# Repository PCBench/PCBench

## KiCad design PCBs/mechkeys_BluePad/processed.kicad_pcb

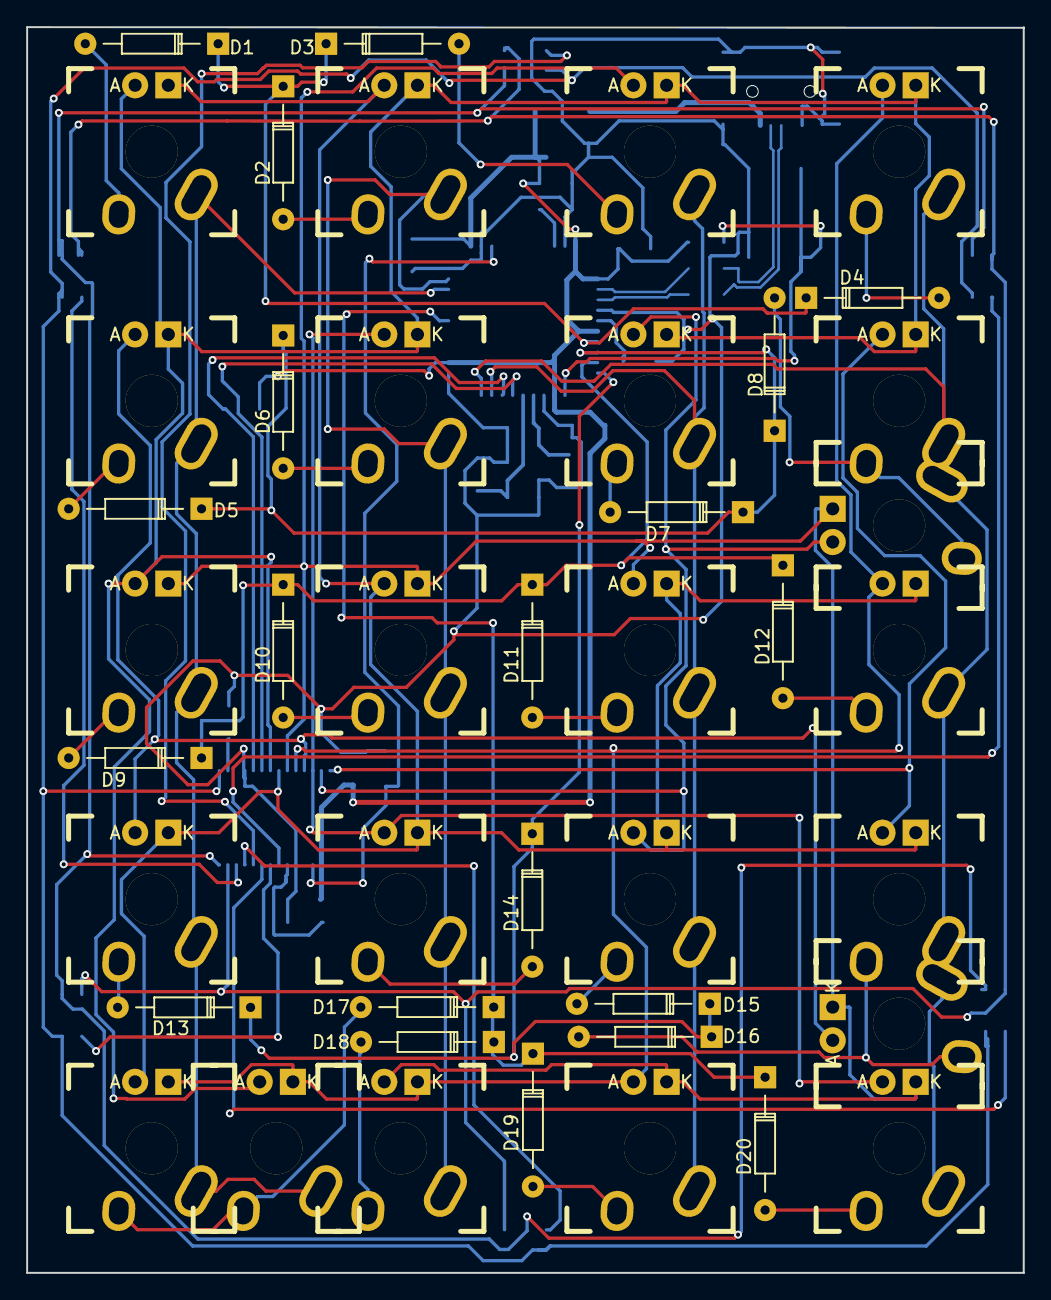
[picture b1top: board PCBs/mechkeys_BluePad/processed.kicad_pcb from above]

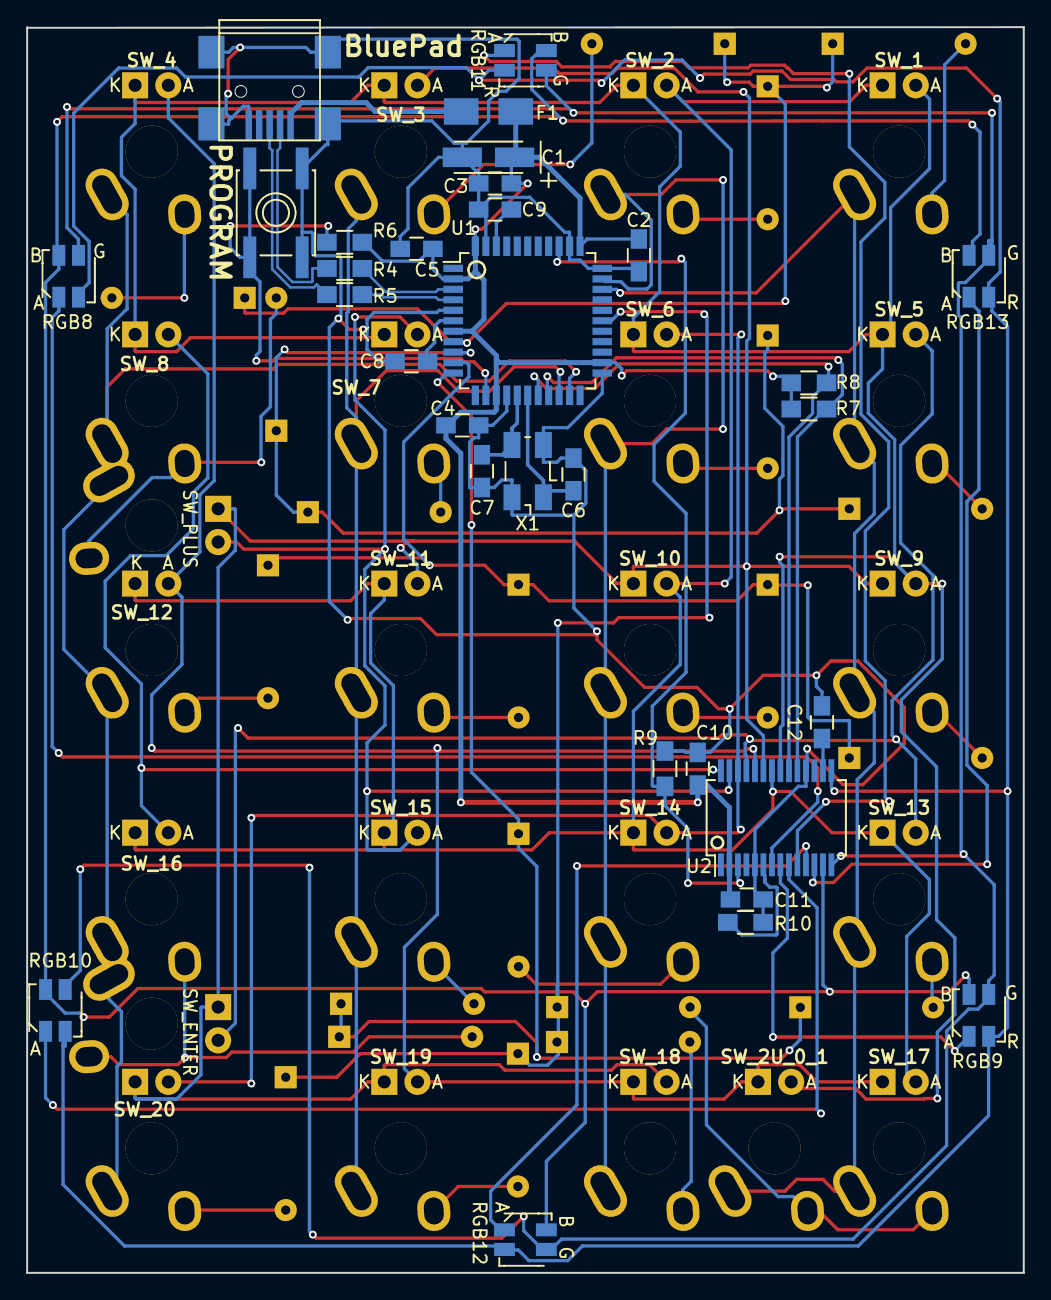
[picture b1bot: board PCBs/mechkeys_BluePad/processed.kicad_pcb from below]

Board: 2 copper layers, 76.2 x 95.2 mm, 74 parts (31 on the bottom side), 63 nets.

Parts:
C1: 10µF; TantalC_SizeA_EIA-3216_HandSoldering
C2, C3, C4, C5, C9, C11, C12: 0.1µF; C_0805_HandSoldering
C6, C7: 18pF; C_0805_HandSoldering
C8, C10: 1µF; C_0805_HandSoldering
D1, D2, D3, D4, D5, D6, D7, D8, D9, D10, D11, D12, D13, D14, D15, D16, D17, D18, D19, D20: D; Diode_DO-35_SOD27_Horizontal_RM10
F1: FP_Small; Fuse_SMD1206_HandSoldering
J1: USB_OTG; USB_Mini-B
R4, R5: 22; R_0805_HandSoldering
R6: 10k; R_0805_HandSoldering
R7, R8: 4.7KΩ; R_0805_HandSoldering
R9: 100KΩ; R_0805_HandSoldering
R10: 20KΩ; R_0805_HandSoldering
RGB8, RGB9, RGB10, RGB11, RGB12, RGB13: Led_RGB_CA; SMP4-RGB
SW1: SW_RST; SW_SPST_EVQP0
SW_1, SW_2, SW_2U_0_1, SW_2U_PLUS_1, SW_3, SW_4, SW_5, SW_6, SW_7, SW_8, SW_9, SW_10, SW_11, SW_12, SW_13, SW_14, SW_15, SW_16, SW_17, SW_18, SW_19, SW_20: MX_LED; MXALPS
SW_2U_ENTER_1: MX_LED; MXALPS_LED_PANEL
U1: ATMEGA32U4RC-A; TQFP-44_10x10mm_Pitch0.8mm
U2: IS31FL3731; SSOP-28_5.3x10.2mm_Pitch0.65mm
X1: 16Mhz; Crystal_SMD_5032_4Pads

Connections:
+5V: C1.1, C2.1, C3.1, C4.1, C5.1, C10.1, C11.1, F1.2, R6.2, R7.1, R8.1, U1.2, U1.7, U1.14, U1.24, U1.34, U1.44, U2.2
C1: SW_1.SW1, SW_2U_0_1.SW1, SW_5.SW1, SW_9.SW1, SW_13.SW1, SW_17.SW1, U1.31
C2: SW_2.SW1, SW_6.SW1, SW_10.SW1, SW_14.SW1, SW_18.SW1, U1.32
C3: SW_3.SW1, SW_7.SW1, SW_11.SW1, SW_15.SW1, SW_19.SW1, U1.20
C4: SW_2U_ENTER_1.SW1, SW_2U_PLUS_1.SW1, SW_4.SW1, SW_8.SW1, SW_12.SW1, SW_16.SW1, SW_20.SW1, U1.21
CA1: SW_1.A, SW_2.K, SW_2U_0_1.A, SW_3.K, SW_4.K, SW_5.K, SW_6.K, SW_7.K, SW_8.K, SW_9.A, U2.21
CA2: SW_1.K, SW_2.A, SW_10.A, SW_11.K, SW_12.K, SW_13.K, SW_14.K, SW_15.K, SW_16.K, SW_17.A, U2.22
CA3: SW_2U_ENTER_1.K, SW_2U_PLUS_1.K, SW_3.A, SW_9.K, SW_10.K, SW_11.A, SW_18.A, SW_19.K, SW_20.K, U2.23
CA4: SW_2U_0_1.K, SW_4.A, SW_12.A, SW_17.K, SW_18.K, SW_19.A, U2.24
CA5: SW_2U_ENTER_1.A, SW_5.A, SW_13.A, U2.25
CA6: SW_6.A, SW_14.A, SW_20.A, U2.26
CA7: SW_2U_PLUS_1.A, SW_7.A, SW_15.A, U2.27
CA8: SW_8.A, SW_16.A, U2.28
CB1: RGB8.1, U2.7
CB2: RGB9.1, U2.8
CB3: RGB10.1, U2.9
CB4: RGB11.1, U2.10
CB5: RGB12.1, U2.11
CB6: RGB13.1, U2.12
CB7: RGB8.4, RGB9.4, RGB10.4, RGB11.4, RGB12.4, RGB13.4, U2.13
CB8: RGB8.3, RGB9.3, RGB10.3, RGB11.3, RGB12.3, RGB13.3, U2.14
CB9: RGB8.2, RGB9.2, RGB10.2, RGB11.2, RGB12.2, RGB13.2, U2.15
D+: R5.1, U1.4
D-: R4.1, U1.3
GND: C1.2, C2.2, C3.2, C4.2, C5.2, C6.2, C7.2, C8.2, C9.2, C10.2, C11.2, C12.2, J1.5, J1.6, R9.2, R10.2, SW1.1, U1.5, U1.15, U1.23, U1.33, U1.35, U1.43, U2.5, U2.18, X1.3
LED_NSRT: R9.1, U1.36, U2.3
LED_SCL: R8.2, U1.18, U2.20
LED_SDA: R7.2, U1.19, U2.19
unnamed: C6.1, U1.17, X1.1
unnamed: C7.1, U1.16, X1.2
unnamed: C8.1, U1.6
unnamed: C9.1, U1.42
unnamed: C12.1, U2.16
unnamed: D1.2, SW_1.SW2
unnamed: D2.2, SW_2.SW2
unnamed: D3.2, SW_3.SW2
unnamed: D4.2, SW_4.SW2
unnamed: D5.2, SW_5.SW2
unnamed: D6.2, SW_6.SW2
unnamed: D7.2, SW_7.SW2
unnamed: D8.2, SW_2U_PLUS_1.SW2, SW_8.SW2
unnamed: D9.2, SW_9.SW2
unnamed: D10.2, SW_10.SW2
unnamed: D11.2, SW_11.SW2
unnamed: D12.2, SW_12.SW2
unnamed: D13.2, SW_13.SW2
unnamed: D14.2, SW_14.SW2
unnamed: D15.2, SW_15.SW2
unnamed: D16.2, SW_2U_ENTER_1.SW2, SW_16.SW2
unnamed: D17.2, SW_2U_0_1.SW2, SW_17.SW2
unnamed: D18.2, SW_18.SW2
unnamed: D19.2, SW_19.SW2
unnamed: D20.2, SW_20.SW2
unnamed: F1.1, J1.1
unnamed: R10.1, U2.6
R1: D1.1, D2.1, D3.1, D4.1, U1.8
R2: D5.1, D6.1, D7.1, D8.1, U1.9
R3: D9.1, D10.1, D11.1, D12.1, U1.10
R4: D13.1, D14.1, D15.1, D16.1, U1.11
R5: D17.1, D18.1, D19.1, D20.1, U1.28
RST: R6.1, SW1.2, U1.13
USB+: J1.3, R5.2
USB-: J1.2, R4.2

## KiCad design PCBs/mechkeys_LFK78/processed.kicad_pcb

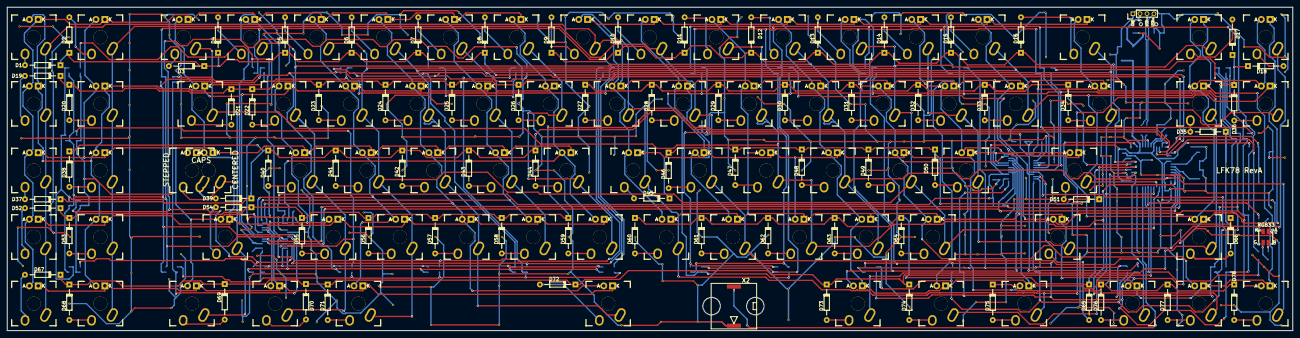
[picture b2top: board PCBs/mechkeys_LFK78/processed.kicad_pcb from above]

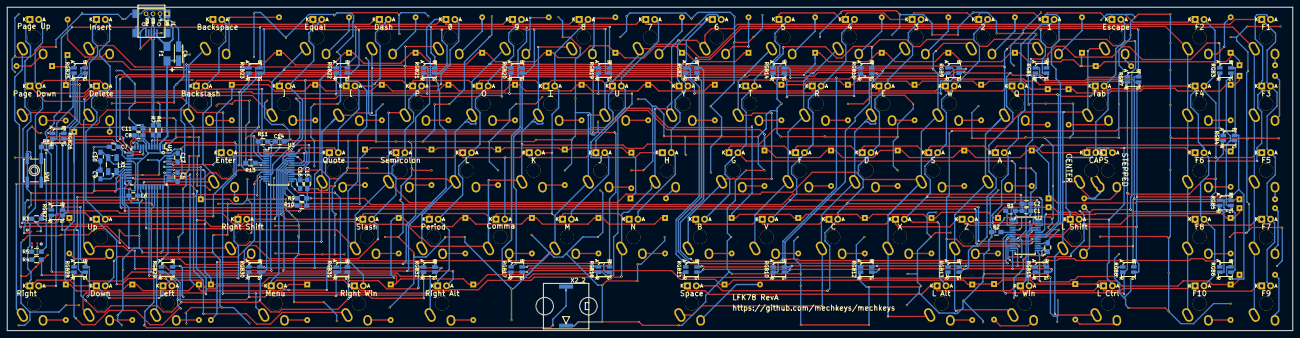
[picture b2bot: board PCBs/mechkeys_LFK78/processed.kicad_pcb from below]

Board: 2 copper layers, 367.8 x 92.5 mm, 226 parts (66 on the bottom side), 159 nets.

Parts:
C1, C11, C14: 1µF; C_0805_HandSoldering
C2, C3, C5, C6, C7, C8, C12, C15, C16: 0.1µF; C_0805_HandSoldering
C4: 10µF; TantalC_SizeA_EIA-3216_HandSoldering
C9, C10: 18pF; C_0805_HandSoldering
CHERRY: MX; CHERRY_PCB_625H_STABILIZER
D1, D2, D3, D4, D5, D6, D7, D8, D9, D10, D11, D12, D13, D14, D15, D16, D17, D18, D19, D20, D21, D22, D23, D24, D25, D26, D27, D28, D29, D30, D31, D32, D33, D34, D35, D36, D37, D38, D39, D40, D41, D42, D43, D44, D45, D46, D47, D48, D49, D50, D51, D52, D53, D54, D55, D56, D57, D58, D59, D60, D61, D62, D63, D64, D65, D66, D67, D68, D69, D70, D71, D72, D73, D74, D75, D76, D77, D78: D; Diode_DO-35_SOD27_Horizontal_RM10
F1: FP_Small; Fuse_SMD1206_HandSoldering
J1: USB_OTG; USB_Mini-B
R1, R11: 10KΩ; R_0805_HandSoldering
R2, R13: 20KΩ; R_0805_HandSoldering
R3: 150Ω; R_0805_HandSoldering
R4, R5: 120Ω; R_0805_HandSoldering
R6, R7: 22; R_0805_HandSoldering
R8: 10k; R_0805_HandSoldering
R9, R10: 4.7KΩ; R_0805_HandSoldering
RGB1, RGB2, RGB3, RGB4, RGB5, RGB6, RGB7, RGB8, RGB9, RGB10, RGB11, RGB12, RGB13, RGB14, RGB15, RGB16, RGB17, RGB18, RGB19, RGB20, RGB21, RGB22, RGB23, RGB25, RGB26, RGB27, RGB28, RGB29, RGB30, RGB31, RGB32: Led_RGB_CA; SMP4-RGB
RGB33: Led_RGB_CA; SMP4-RGB-PIPE
SW1: SW_RST; SW_SPST_EVQP0
SW_A_40: MX_LED; MXALPS_LED_PANEL
SW_Alt_71, SW_Alt_73: MX_LED; MXALPS_LED_PANEL
SW_B_59: MX_LED; MXALPS_LED_PANEL
SW_Backspace_16: MX_LED; MXALPS_LED_PANEL
SW_C_57: MX_LED; MXALPS_LED_PANEL
SW_CapStep_39: MX_LED; MXALPS_LED_PANEL
SW_Caps_39: MX_LED; MXALPS_LED_PANEL
SW_Ctrl_69: MX_LED; MXALPS_LED_PANEL
SW_D_42: MX_LED; MXALPS_LED_PANEL
SW_Del_35: MX_LED; MXALPS_LED_PANEL
SW_E_24: MX_LED; MXALPS_LED_PANEL
SW_Enter_51: MX_LED; MXALPS_LED_PANEL
SW_F1_1, SW_F2_2, SW_F3_19, SW_F4_20, SW_F5_37, SW_F6_38, SW_F7_52, SW_F8_53, SW_F9_67, SW_F10_68: MX_LED; MXALPS_LED_PANEL
SW_F_43: MX_LED; MXALPS_LED_PANEL
SW_G_44: MX_LED; MXALPS_LED_PANEL
SW_H_45: MX_LED; MXALPS_LED_PANEL
SW_I_29: MX_LED; MXALPS_LED_PANEL
SW_Ins_17: MX_LED; MXALPS_LED_PANEL
SW_J_46: MX_LED; MXALPS_LED_PANEL
SW_K_47: MX_LED; MXALPS_LED_PANEL
SW_L_48: MX_LED; MXALPS_LED_PANEL
SW_M_61: MX_LED; MXALPS_LED_PANEL
SW_Menu_75: MX_LED; MXALPS_LED_PANEL
SW_N_60: MX_LED; MXALPS_LED_PANEL
SW_O_30: MX_LED; MXALPS_LED_PANEL
SW_P_31: MX_LED; MXALPS_LED_PANEL
SW_PgDn_36: MX_LED; MXALPS_LED_PANEL
SW_PgUp_18: MX_LED; MXALPS_LED_PANEL
SW_Q_22: MX_LED; MXALPS_LED_PANEL
SW_R_25: MX_LED; MXALPS_LED_PANEL
SW_S_41: MX_LED; MXALPS_LED_PANEL
SW_Shift_54, SW_Shift_65: MX_LED; MXALPS_LED_PANEL
SW_T_26: MX_LED; MXALPS_LED_PANEL
SW_Tab_21: MX_LED; MXALPS_LED_PANEL
SW_U_28: MX_LED; MXALPS_LED_PANEL
SW_V_58: MX_LED; MXALPS_LED_PANEL
SW_W_23: MX_LED; MXALPS_LED_PANEL
SW_Win_70, SW_Win_74: MX_LED; MXALPS_LED_PANEL
SW_X4Y1_3, SW_X5Y1_4, SW_X6Y1_5, SW_X7Y1_6, SW_X8Y1_7, SW_X8Y5_72, SW_X9Y1_8, SW_X10Y1_9, SW_X11Y1_10, SW_X12Y1_11, SW_X13Y1_12, SW_X13Y4_62, SW_X14Y1_13, SW_X14Y4_63, SW_X15Y1_14, SW_X15Y2_32, SW_X15Y3_49, SW_X15Y4_64, SW_X16Y1_15, SW_X16Y2_33, SW_X16Y3_50, SW_X17Y2_34, SW_X18Y5_76, SW_X19Y4_66, SW_X19Y5_77, SW_X20Y5_78: MX_LED; MXALPS_LED_PANEL
SW_X_56: MX_LED; MXALPS_LED_PANEL
SW_Y_27: MX_LED; MXALPS_LED_PANEL
SW_Z_55: MX_LED; MXALPS_LED_PANEL
U1: ATMEGA32U4RC-A; TQFP-44_10x10mm_Pitch0.8mm
U2, U3: IS31FL3731; SSOP-28_5.3x10.2mm_Pitch0.65mm
X1: 16Mhz; Crystal_SMD_5032_4Pads
X2, X2_2: PiezoelectricCrystal-TwoElectrodes_EN60617_04-07-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; piezo-12x12

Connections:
+5V: C1.1, C2.1, C4.1, C5.1, C6.1, C7.1, C8.1, C14.1, C15.1, F1.2, R1.2, R8.2, R9.1, R10.1, R11.2, RGB33.1, U1.2, U1.7, U1.14, U1.24, U1.34, U1.44, U2.2, U3.2, U3.18
AUDIO: U1.31, X2.2, X2_2.2
C1: SW_F1_1.SW1, SW_F3_19.SW1, SW_F5_37.SW1, SW_F7_52.SW1, SW_F9_67.SW1, SW_H_45.SW1, SW_Menu_75.SW1, SW_N_60.SW1, SW_X10Y1_9.SW1, SW_Y_27.SW1, U1.1
C2: SW_F2_2.SW1, SW_F4_20.SW1, SW_F6_38.SW1, SW_F8_53.SW1, SW_F10_68.SW1, SW_J_46.SW1, SW_M_61.SW1, SW_U_28.SW1, SW_X11Y1_10.SW1, SW_X18Y5_76.SW1, U1.36
C3: SW_CapStep_39.SW2, SW_Caps_39.SW1, SW_Ctrl_69.SW1, SW_I_29.SW1, SW_K_47.SW1, SW_Shift_54.SW1, SW_Tab_21.SW1, SW_X4Y1_3.SW1, SW_X12Y1_11.SW1, SW_X13Y4_62.SW1, SW_X19Y5_77.SW1, U1.20
C4: SW_A_40.SW1, SW_L_48.SW1, SW_O_30.SW1, SW_Q_22.SW1, SW_Win_70.SW1, SW_X5Y1_4.SW1, SW_X13Y1_12.SW1, SW_X14Y4_63.SW1, SW_X20Y5_78.SW1, SW_Z_55.SW1, U1.21
C5: SW_Alt_71.SW1, SW_Ins_17.SW1, SW_P_31.SW1, SW_S_41.SW1, SW_W_23.SW1, SW_X6Y1_5.SW1, SW_X14Y1_13.SW1, SW_X15Y3_49.SW1, SW_X15Y4_64.SW1, SW_X_56.SW1, U1.25
C6: SW_C_57.SW1, SW_D_42.SW1, SW_E_24.SW1, SW_PgUp_18.SW1, SW_Shift_65.SW1, SW_X7Y1_6.SW1, SW_X8Y5_72.SW1, SW_X15Y1_14.SW1, SW_X15Y2_32.SW1, SW_X16Y3_50.SW1, U1.22
C7: SW_Alt_73.SW1, SW_Del_35.SW1, SW_Enter_51.SW1, SW_F_43.SW1, SW_R_25.SW1, SW_V_58.SW1, SW_X8Y1_7.SW1, SW_X16Y1_15.SW1, SW_X16Y2_33.SW1, SW_X19Y4_66.SW1, U1.26
C8: SW_B_59.SW1, SW_Backspace_16.SW1, SW_G_44.SW1, SW_PgDn_36.SW1, SW_T_26.SW1, SW_Win_74.SW1, SW_X9Y1_8.SW1, SW_X17Y2_34.SW1, U1.27
D+: R7.1, U1.4
D-: R6.1, U1.3
GND: C1.2, C2.2, C3.2, C4.2, C5.2, C6.2, C7.2, C8.2, C9.2, C10.2, C11.2, C12.2, C14.2, C15.2, C16.2, J1.5, J1.6, R2.2, R13.2, SW1.1, U1.5, U1.15, U1.23, U1.33, U1.35, U1.43, U2.5, U2.18, U3.5, X2.1, X2_2.1
LED_SCL: R10.2, U1.18, U2.20, U3.20
LED_SDA: R9.2, U1.19, U2.19, U3.19
L_CA1: SW_F1_1.K, SW_F2_2.K, SW_F3_19.A, SW_F5_37.A, SW_F7_52.A, SW_F9_67.A, SW_X4Y1_3.K, SW_X5Y1_4.K, SW_X6Y1_5.K, SW_X7Y1_6.K, SW_X8Y1_7.K, SW_X9Y1_8.K, U2.21
L_CA2: SW_E_24.K, SW_F1_1.A, SW_F3_19.K, SW_F4_20.K, SW_F6_38.A, SW_F8_53.A, SW_F10_68.A, SW_Q_22.K, SW_R_25.K, SW_T_26.K, SW_Tab_21.K, SW_W_23.K, U2.22
L_CA3: SW_A_40.K, SW_CapStep_39.K, SW_Caps_39.K, SW_Ctrl_69.A, SW_D_42.K, SW_F2_2.A, SW_F4_20.A, SW_F5_37.K, SW_F6_38.K, SW_F_43.K, SW_G_44.K, SW_S_41.K, SW_Shift_54.A, U2.23
L_CA4: SW_B_59.K, SW_C_57.K, SW_CapStep_39.A, SW_Caps_39.A, SW_F7_52.K, SW_F8_53.K, SW_Shift_54.K, SW_Tab_21.A, SW_V_58.K, SW_Win_70.A, SW_X4Y1_3.A, SW_X_56.K, SW_Z_55.K, U2.24
L_CA5: SW_A_40.A, SW_Alt_71.K, SW_Ctrl_69.K, SW_F9_67.K, SW_F10_68.K, SW_Q_22.A, SW_Win_70.K, SW_X5Y1_4.A, SW_X8Y5_72.K, SW_Z_55.A, U2.25
L_CA6: SW_Alt_71.A, SW_S_41.A, SW_W_23.A, SW_X6Y1_5.A, SW_X_56.A, U2.26
L_CA7: SW_C_57.A, SW_D_42.A, SW_E_24.A, SW_X7Y1_6.A, SW_X8Y5_72.A, U2.27
L_CA8: SW_F_43.A, SW_R_25.A, SW_V_58.A, SW_X8Y1_7.A, U2.28
L_CA9: SW_B_59.A, SW_G_44.A, SW_T_26.A, SW_X9Y1_8.A, U2.1
L_CB1: RGB1.2, RGB2.2, RGB3.2, RGB4.2, RGB5.2, RGB6.2, RGB7.2, RGB8.2, RGB9.1, U2.7
L_CB2: RGB1.1, RGB2.3, RGB3.3, RGB4.3, RGB5.3, RGB6.3, RGB7.3, RGB8.3, RGB10.1, U2.8
L_CB3: RGB1.3, RGB2.1, RGB3.4, RGB4.4, RGB5.4, RGB6.4, RGB7.4, RGB8.4, RGB11.1, U2.9
L_CB4: RGB1.4, RGB2.4, RGB3.1, RGB12.1, U2.10
L_CB5: RGB4.1, RGB13.1, U2.11
L_CB6: RGB5.1, RGB14.1, RGB15.4, RGB16.4, U2.12
L_CB7: RGB6.1, RGB9.4, RGB10.4, RGB11.4, RGB12.4, RGB13.4, RGB14.4, RGB15.1, RGB16.3, U2.13
L_CB8: RGB7.1, RGB9.3, RGB10.3, RGB11.3, RGB12.3, RGB13.3, RGB14.3, RGB15.3, RGB16.1, U2.14
L_CB9: RGB8.1, RGB9.2, RGB10.2, RGB11.2, RGB12.2, RGB13.2, RGB14.2, RGB15.2, RGB16.2, U2.15
unnamed: C3.1, U2.16
unnamed: C9.1, U1.17, X1.1
unnamed: C10.1, U1.16, X1.2
unnamed: C11.1, U1.6
unnamed: C12.1, U1.42
unnamed: C16.1, U3.16
unnamed: D1.2, SW_F1_1.SW2
unnamed: D2.2, SW_F2_2.SW2
unnamed: D3.2, SW_X4Y1_3.SW2
unnamed: D4.2, SW_X5Y1_4.SW2
unnamed: D5.2, SW_X6Y1_5.SW2
unnamed: D6.2, SW_X7Y1_6.SW2
unnamed: D7.2, SW_X8Y1_7.SW2
unnamed: D8.2, SW_X9Y1_8.SW2
unnamed: D9.2, SW_X10Y1_9.SW2
unnamed: D10.2, SW_X11Y1_10.SW2
unnamed: D11.2, SW_X12Y1_11.SW2
unnamed: D12.2, SW_X13Y1_12.SW2
unnamed: D13.2, SW_X14Y1_13.SW2
unnamed: D14.2, SW_X15Y1_14.SW2
unnamed: D15.2, SW_X16Y1_15.SW2
unnamed: D16.2, SW_Backspace_16.SW2
unnamed: D17.2, SW_Ins_17.SW2
unnamed: D18.2, SW_PgUp_18.SW2
unnamed: D19.2, SW_F3_19.SW2
unnamed: D20.2, SW_F4_20.SW2
unnamed: D21.2, SW_Tab_21.SW2
unnamed: D22.2, SW_Q_22.SW2
unnamed: D23.2, SW_W_23.SW2
unnamed: D24.2, SW_E_24.SW2
unnamed: D25.2, SW_R_25.SW2
unnamed: D26.2, SW_T_26.SW2
unnamed: D27.2, SW_Y_27.SW2
unnamed: D28.2, SW_U_28.SW2
unnamed: D29.2, SW_I_29.SW2
unnamed: D30.2, SW_O_30.SW2
unnamed: D31.2, SW_P_31.SW2
unnamed: D32.2, SW_X15Y2_32.SW2
unnamed: D33.2, SW_X16Y2_33.SW2
unnamed: D34.2, SW_X17Y2_34.SW2
unnamed: D35.2, SW_Del_35.SW2
unnamed: D36.2, SW_PgDn_36.SW2
unnamed: D37.2, SW_F5_37.SW2
unnamed: D38.2, SW_F6_38.SW2
unnamed: D39.2, SW_CapStep_39.SW1, SW_Caps_39.SW2
unnamed: D40.2, SW_A_40.SW2
unnamed: D41.2, SW_S_41.SW2
unnamed: D42.2, SW_D_42.SW2
unnamed: D43.2, SW_F_43.SW2
unnamed: D44.2, SW_G_44.SW2
unnamed: D45.2, SW_H_45.SW2
unnamed: D46.2, SW_J_46.SW2
unnamed: D47.2, SW_K_47.SW2
unnamed: D48.2, SW_L_48.SW2
unnamed: D49.2, SW_X15Y3_49.SW2
unnamed: D50.2, SW_X16Y3_50.SW2
unnamed: D51.2, SW_Enter_51.SW2
unnamed: D52.2, SW_F7_52.SW2
unnamed: D53.2, SW_F8_53.SW2
unnamed: D54.2, SW_Shift_54.SW2
unnamed: D55.2, SW_Z_55.SW2
unnamed: D56.2, SW_X_56.SW2
unnamed: D57.2, SW_C_57.SW2
unnamed: D58.2, SW_V_58.SW2
unnamed: D59.2, SW_B_59.SW2
unnamed: D60.2, SW_N_60.SW2
unnamed: D61.2, SW_M_61.SW2
unnamed: D62.2, SW_X13Y4_62.SW2
unnamed: D63.2, SW_X14Y4_63.SW2
unnamed: D64.2, SW_X15Y4_64.SW2
unnamed: D65.2, SW_Shift_65.SW2
unnamed: D66.2, SW_X19Y4_66.SW2
unnamed: D67.2, SW_F9_67.SW2
unnamed: D68.2, SW_F10_68.SW2
unnamed: D69.2, SW_Ctrl_69.SW2
unnamed: D70.2, SW_Win_70.SW2
unnamed: D71.2, SW_Alt_71.SW2
unnamed: D72.2, SW_X8Y5_72.SW2
unnamed: D73.2, SW_Alt_73.SW2
unnamed: D74.2, SW_Win_74.SW2
unnamed: D75.2, SW_Menu_75.SW2
unnamed: D76.2, SW_X18Y5_76.SW2
unnamed: D77.2, SW_X19Y5_77.SW2
unnamed: D78.2, SW_X20Y5_78.SW2
unnamed: F1.1, J1.1
unnamed: R1.1, U2.3
unnamed: R2.1, U2.6
unnamed: R3.1, RGB33.2
unnamed: R4.1, RGB33.3
unnamed: R5.1, RGB33.4
unnamed: R11.1, U3.3
unnamed: R13.1, U3.6
PWM_BLUE: R5.2, U1.12
PWM_GREEN: R4.2, U1.30
PWM_RED: R3.2, U1.29
R1: D1.1, D2.1, D3.1, D4.1, D5.1, D6.1, D7.1, D8.1, U1.8
R2/SCK: D19.1, D20.1, D21.1, D22.1, D23.1, D24.1, D25.1, D26.1, U1.9
R3/MOSI: D37.1, D38.1, D39.1, D40.1, D41.1, D42.1, D43.1, D44.1, U1.10
R4/MISO: D52.1, D53.1, D54.1, D55.1, D56.1, D57.1, D58.1, D59.1, U1.11
R5: D67.1, D68.1, D69.1, D70.1, D71.1, D72.1, D73.1, D74.1, U1.28
R6: D9.1, D10.1, D11.1, D12.1, D13.1, D14.1, D15.1, D16.1, U1.41
R7: D27.1, D28.1, D29.1, D30.1, D31.1, D32.1, D33.1, D34.1, U1.40
R8: D45.1, D46.1, D47.1, D48.1, D49.1, D50.1, D51.1, U1.39
R9: D60.1, D61.1, D62.1, D63.1, D64.1, D65.1, D66.1, U1.38
R10: D17.1, D18.1, D35.1, D36.1, D75.1, D76.1, D77.1, D78.1, U1.37
RST: R8.1, SW1.2, U1.13
R_CA1: SW_Alt_73.A, SW_Backspace_16.K, SW_H_45.A, SW_N_60.A, SW_X10Y1_9.K, SW_X11Y1_10.K, SW_X12Y1_11.K, SW_X13Y1_12.K, SW_X14Y1_13.K, SW_X15Y1_14.K, SW_X16Y1_15.K, SW_Y_27.A, U3.21
R_CA2: SW_I_29.K, SW_J_46.A, SW_M_61.A, SW_O_30.K, SW_P_31.K, SW_U_28.K, SW_Win_74.A, SW_X10Y1_9.A, SW_X15Y2_32.K, SW_X16Y2_33.K, SW_X17Y2_34.K, SW_Y_27.K, U3.22
R_CA3: SW_Enter_51.K, SW_H_45.K, SW_J_46.K, SW_K_47.K, SW_L_48.K, SW_Menu_75.A, SW_PgDn_36.K, SW_U_28.A, SW_X11Y1_10.A, SW_X13Y4_62.A, SW_X15Y3_49.K, SW_X16Y3_50.K, U3.23
R_CA4: SW_I_29.A, SW_K_47.A, SW_M_61.K, SW_N_60.K, SW_PgUp_18.K, SW_Shift_65.K, SW_X12Y1_11.A, SW_X13Y4_62.K, SW_X14Y4_63.K, SW_X15Y4_64.K, SW_X18Y5_76.A, SW_X19Y4_66.K, U3.24
R_CA5: SW_Alt_73.K, SW_Del_35.K, SW_Ins_17.K, SW_L_48.A, SW_Menu_75.K, SW_O_30.A, SW_Win_74.K, SW_X13Y1_12.A, SW_X14Y4_63.A, SW_X18Y5_76.K, SW_X19Y5_77.K, SW_X20Y5_78.K, U3.25
R_CA6: SW_P_31.A, SW_X14Y1_13.A, SW_X15Y3_49.A, SW_X15Y4_64.A, SW_X19Y5_77.A, U3.26
R_CA7: SW_Shift_65.A, SW_X15Y1_14.A, SW_X15Y2_32.A, SW_X16Y3_50.A, SW_X20Y5_78.A, U3.27
R_CA8: SW_Enter_51.A, SW_Ins_17.A, SW_X16Y1_15.A, SW_X16Y2_33.A, SW_X19Y4_66.A, U3.28
R_CA9: SW_Backspace_16.A, SW_Del_35.A, SW_PgDn_36.A, SW_PgUp_18.A, SW_X17Y2_34.A, U3.1
R_CB1: RGB17.2, RGB18.2, RGB19.2, RGB20.2, RGB21.2, RGB22.2, RGB23.2, RGB25.1, U3.7
R_CB2: RGB17.1, RGB18.3, RGB19.3, RGB20.3, RGB21.3, RGB22.3, RGB23.3, RGB26.1, U3.8
R_CB3: RGB17.3, RGB18.1, RGB19.4, RGB20.4, RGB21.4, RGB22.4, RGB23.4, RGB27.1, U3.9
R_CB4: RGB17.4, RGB18.4, RGB19.1, RGB28.1, U3.10
R_CB5: RGB20.1, RGB29.1, U3.11
R_CB6: RGB21.1, RGB30.1, RGB31.4, RGB32.4, U3.12
R_CB7: RGB22.1, RGB25.4, RGB26.4, RGB27.4, RGB28.4, RGB29.4, RGB30.4, RGB31.1, RGB32.3, U3.13
R_CB8: RGB23.1, RGB25.3, RGB26.3, RGB27.3, RGB28.3, RGB29.3, RGB30.3, RGB31.3, RGB32.1, U3.14
R_CB9: RGB25.2, RGB26.2, RGB27.2, RGB28.2, RGB29.2, RGB30.2, RGB31.2, RGB32.2, U3.15
USB+: J1.3, R7.2
USB-: J1.2, R6.2

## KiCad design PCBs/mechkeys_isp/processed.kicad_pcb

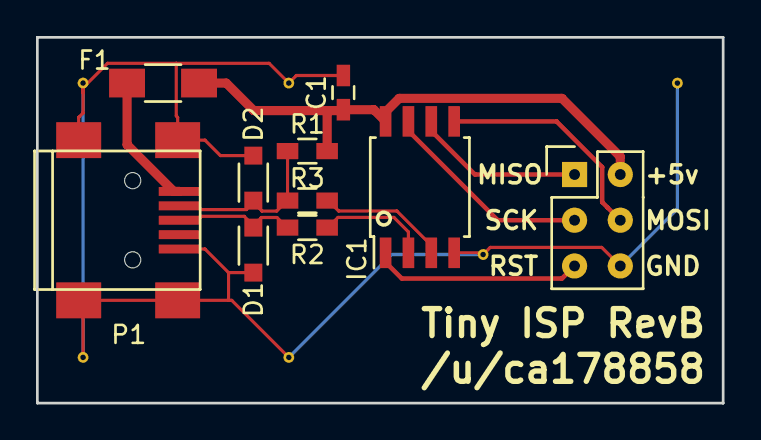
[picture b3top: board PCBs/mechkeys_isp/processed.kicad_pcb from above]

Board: 2 copper layers, 38.1 x 20.3 mm, 10 parts (0 on the bottom side), 11 nets.

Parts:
C1: 0.1µF; C_0603_HandSoldering
D1, D2: 3.6v; SOD-323_HandSoldering
F1: F_Small; C_1206_HandSoldering
IC1: ATTINY45-S; SOIJ-8_5.3x5.3mm_Pitch1.27mm
P1: USB_OTG; USB_Mini-B
P2: CONN_02X03; Pin_Header_Straight_2x03
R1: 1.7kΩ; R_0603_HandSoldering
R2, R3: 68Ω; R_0603_HandSoldering

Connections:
+5V: C1.1, F1.1, IC1.8, P2.2, R1.1
D+: D1.1, P1.3, R2.2
D-: D2.1, P1.2, R1.2, R3.2
GND: C1.2, D1.2, D2.2, IC1.4, P1.5, P1.6, P2.6
MISO: IC1.6, P2.1
MOSI: IC1.5, P2.4
unnamed: F1.2, P1.1
unnamed: IC1.2, R2.1
unnamed: IC1.3, R3.1
RST: IC1.1, P2.5
SCK: IC1.7, P2.3

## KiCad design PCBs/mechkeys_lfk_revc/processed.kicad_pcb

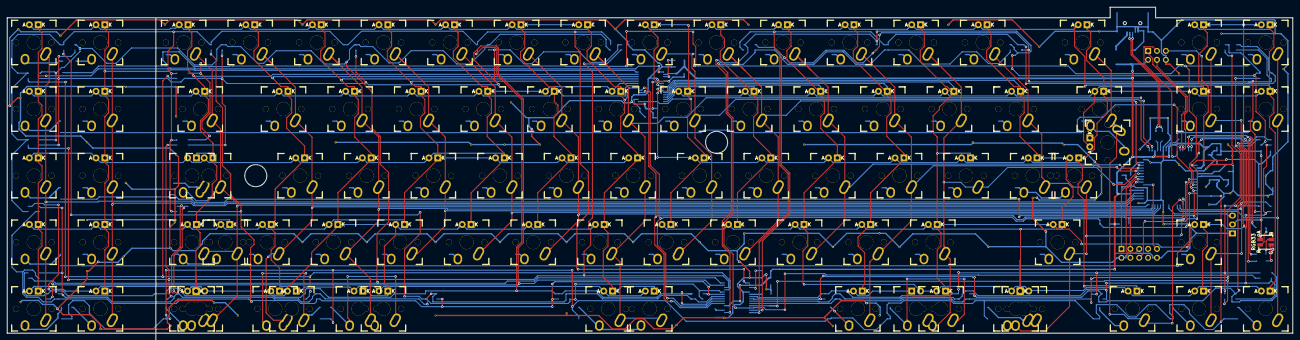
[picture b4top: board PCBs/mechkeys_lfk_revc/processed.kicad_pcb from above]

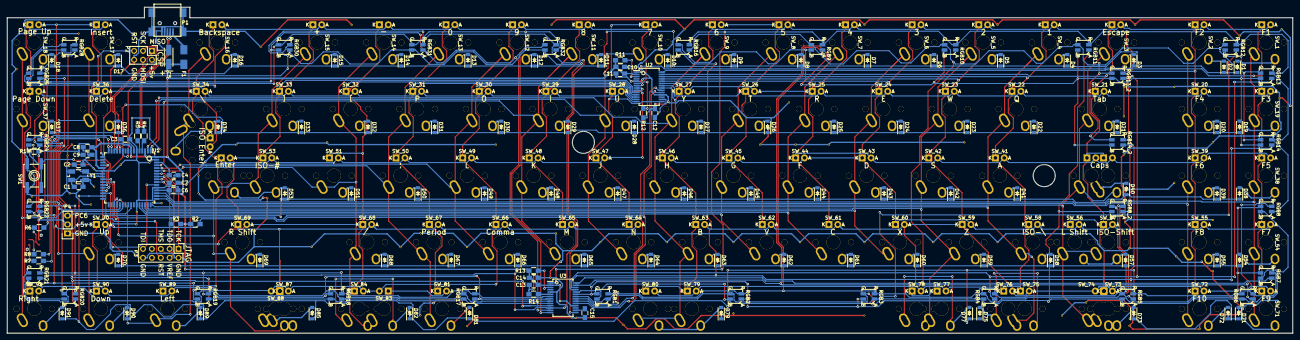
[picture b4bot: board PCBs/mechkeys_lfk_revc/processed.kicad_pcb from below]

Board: 2 copper layers, 367.8 x 93.2 mm, 238 parts (146 on the bottom side), 172 nets.

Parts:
C1, C2: 18pF; C_0805_HandSoldering
C3, C6, C7, C8, C9, C11, C12, C14, C15: 0.1µF; C_0805_HandSoldering
C4, C10, C13: 1µF; C_0805_HandSoldering
C5: 4.7µF; TantalC_SizeA_EIA-3216_HandSoldering
D1, D2, D3, D4, D5, D6, D7, D8, D9, D10, D11, D12, D13, D14, D15, D16, D17, D18, D19, D20, D21, D22, D23, D24, D25, D26, D27, D28, D29, D30, D31, D32, D33, D34, D36, D37, D38, D39, D40, D41, D42, D43, D44, D45, D46, D47, D48, D49, D50, D51, D53, D54, D55, D57, D58, D59, D60, D61, D62, D63, D64, D65, D66, D67, D68, D69, D70, D71, D72, D73, D75, D77, D79, D81, D82, D85, D89, D90, D91: D; SOD-123
F1: FP_Small; Fuse_SMD1206_HandSoldering
P1: USB_B; USB_Mini-B
P2: CONN_02X03; Pin_Header_Straight_2x03
P3: CONN_02X05; Pin_Header_Straight_2x05
P4: CONN_01X03; Pin_Header_Straight_1x03
R1: 10kΩ; R_0805_HandSoldering
R2, R3: 4.7kΩ; R_0805_HandSoldering
R4, R5: 22Ω; R_0805_HandSoldering
R6: 150; R_0805_HandSoldering
R7, R8: 120; R_0805_HandSoldering
R11, R13: 10KΩ; R_0805_HandSoldering
R12, R14: 20KΩ; R_0805_HandSoldering
RGB1, RGB2, RGB3, RGB4, RGB5, RGB6, RGB7, RGB8, RGB8_2, RGB9, RGB10, RGB11, RGB12, RGB13, RGB13_2, RGB14, RGB14_2, RGB16, RGB17, RGB18, RGB19, RGB20, RGB21, RGB22, RGB24, RGB25, RGB28, RGB30, RGB31, RGB32: Led_RGB_CA; SMP4-RGB
RGB33: Led_RGB_CA; SMP4-RGB-PIPE
STA: Stabilizer; CHERRY_PCB_200_STABILIZER_OUTLINE
STA_2: Stabilizer; CHERRY_PCB_200_STABILIZER_OUTLINE
SW1: SW_PUSH; SW_SPST_EVQP0
SW_1, SW_2, SW_3, SW_4, SW_5, SW_6, SW_7, SW_8, SW_9, SW_10, SW_11, SW_12, SW_13, SW_14, SW_15, SW_16, SW_17, SW_18, SW_19, SW_20, SW_21, SW_22, SW_23, SW_24, SW_25, SW_26, SW_27, SW_28, SW_29, SW_30, SW_31, SW_32, SW_33, SW_34, SW_35, SW_36, SW_37, SW_38, SW_39, SW_40, SW_40_2, SW_41, SW_42, SW_43, SW_44, SW_45, SW_46, SW_47, SW_48, SW_49, SW_50, SW_51, SW_52, SW_53, SW_54, SW_55, SW_56, SW_57, SW_58, SW_59, SW_60, SW_61, SW_62, SW_63, SW_64, SW_65, SW_66, SW_67, SW_68, SW_69, SW_70, SW_71, SW_72, SW_73, SW_75, SW_76, SW_77, SW_78, SW_79, SW_80, SW_81, SW_84, SW_87, SW_89, SW_90, SW_91: MX_LED; MXALPS
SW_74, SW_83, SW_88: MX_LED; MXALPS_REVERSE_LED
U1: AT90USB1286; TQFP-64_14x14mm_Pitch0.8mm
U2, U3: IS31FL3731; SSOP-28_5.3x10.2mm_Pitch0.65mm
Y1: 16Mhz; Crystal_SMD_5032_4Pads

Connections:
+5V: C5.1, C6.1, C7.1, C8.1, C9.1, C10.1, C11.1, C13.1, C14.1, F1.2, P2.2, P3.4, P4.2, R1.1, R2.1, R3.1, R11.2, R13.2, RGB33.1, U1.3, U1.8, U1.21, U1.52, U1.64, U2.2, U3.2, U3.18
AUDIO: P4.3, U1.41
C1: SW_1.SW1, SW_19.SW1, SW_38.SW1, SW_54.SW1, SW_71.SW1, U1.51
C2: SW_2.SW1, SW_20.SW1, SW_39.SW1, SW_55.SW1, SW_72.SW1, U1.50
C3: SW_3.SW1, SW_21.SW1, SW_40.SW1, SW_40_2.SW2, SW_56.SW1, SW_57.SW1, SW_73.SW1, SW_74.SW1, U1.49
C4: SW_4.SW1, SW_22.SW1, SW_41.SW1, SW_58.SW1, SW_75.SW1, SW_76.SW2, U1.48
C5: SW_5.SW1, SW_23.SW1, SW_42.SW1, SW_59.SW1, SW_77.SW1, SW_78.SW2, U1.47
C6: SW_6.SW1, SW_24.SW1, SW_43.SW1, SW_60.SW1, U1.46
C7: SW_7.SW1, SW_25.SW1, SW_44.SW1, SW_61.SW1, U1.45
C8: SW_8.SW1, SW_26.SW1, SW_45.SW1, SW_62.SW1, U1.44
C9: SW_9.SW1, SW_27.SW1, SW_46.SW1, SW_63.SW1, SW_79.SW1, SW_80.SW1, U1.1
C10: SW_10.SW1, SW_28.SW1, SW_47.SW1, SW_64.SW1, U1.2
C11: SW_11.SW1, SW_29.SW1, SW_48.SW1, SW_65.SW1, U1.61
C12: SW_12.SW1, SW_30.SW1, SW_49.SW1, SW_66.SW1, U1.60
C13: SW_13.SW1, SW_31.SW1, SW_50.SW1, SW_67.SW1, SW_81.SW1, U1.59
C14: SW_14.SW1, SW_32.SW1, SW_51.SW1, SW_68.SW1, SW_83.SW1, SW_84.SW2, U1.58
C15: SW_15.SW1, SW_33.SW1, SW_52.SW1, SW_53.SW1, SW_69.SW1, SW_87.SW2, SW_88.SW2, U1.35
C16: SW_16.SW1, SW_34.SW1, SW_35.SW1, SW_89.SW1, U1.36
C17: SW_17.SW1, SW_36.SW1, SW_70.SW1, SW_90.SW1, U1.37
C18: SW_18.SW1, SW_37.SW1, SW_91.SW1, U1.38
D+: R5.1, U1.5
D-: R4.1, U1.4
GND: C1.2, C2.2, C3.2, C4.2, C5.2, C6.2, C7.2, C8.2, C9.2, C10.2, C11.2, C12.2, C13.2, C14.2, C15.2, P1.4, P1.5, P1.6, P2.6, P3.2, P3.10, P4.1, R12.2, R14.2, SW1.1, U1.6, U1.22, U1.43, U1.53, U1.63, U2.5, U2.18, U3.5, Y1.3
LED_SCL: R2.2, U1.25, U2.20, U3.20
LED_SDA: R3.2, U1.26, U2.19, U3.19
L_CA1: SW_1.A, SW_2.A, SW_3.A, SW_4.A, SW_5.A, SW_6.A, SW_7.A, SW_8.A, SW_9.K, SW_27.K, SW_46.K, SW_63.K, SW_79.K, SW_80.K, U2.21
L_CA2: SW_8.K, SW_9.A, SW_19.A, SW_20.A, SW_21.A, SW_22.A, SW_23.A, SW_24.A, SW_25.A, SW_26.K, SW_45.K, SW_62.K, U2.22
L_CA3: SW_7.K, SW_25.K, SW_26.A, SW_27.A, SW_38.A, SW_39.A, SW_40.A, SW_40_2.A, SW_41.A, SW_42.A, SW_43.A, SW_44.K, SW_61.K, U2.23
L_CA4: SW_6.K, SW_24.K, SW_43.K, SW_44.A, SW_45.A, SW_46.A, SW_54.A, SW_55.A, SW_56.A, SW_57.A, SW_58.A, SW_59.A, SW_60.K, U2.24
L_CA5: SW_5.K, SW_23.K, SW_42.K, SW_59.K, SW_60.A, SW_61.A, SW_62.A, SW_63.A, SW_71.A, SW_72.A, SW_73.A, SW_74.A, SW_75.A, SW_76.A, SW_77.K, SW_78.K, U2.25
L_CA6: SW_4.K, SW_22.K, SW_41.K, SW_58.K, SW_75.K, SW_76.K, SW_77.A, SW_78.A, SW_79.A, SW_80.A, U2.26
L_CA7: SW_3.K, SW_21.K, SW_40.K, SW_40_2.K, SW_56.K, SW_57.K, SW_73.K, SW_74.K, U2.27
L_CA8: SW_2.K, SW_20.K, SW_39.K, SW_55.K, SW_72.K, U2.28
L_CA9: SW_1.K, SW_19.K, SW_38.K, SW_54.K, SW_71.K, U2.1
L_CB1: SW_10.A, SW_11.A, SW_12.A, SW_13.A, SW_14.A, SW_15.A, SW_16.A, SW_17.A, SW_18.K, SW_37.K, SW_91.K, U2.7
L_CB2: SW_17.K, SW_18.A, SW_28.A, SW_29.A, SW_30.A, SW_31.A, SW_32.A, SW_33.A, SW_34.A, SW_35.A, SW_36.K, SW_70.K, SW_90.K, U2.8
L_CB3: SW_16.K, SW_34.K, SW_35.K, SW_36.A, SW_37.A, SW_47.A, SW_48.A, SW_49.A, SW_50.A, SW_51.A, SW_52.K, SW_53.A, SW_89.K, U2.9
L_CB4: SW_15.K, SW_33.K, SW_52.A, SW_53.K, SW_64.A, SW_65.A, SW_66.A, SW_67.A, SW_68.A, SW_69.K, SW_87.K, SW_88.K, U2.10
L_CB5: SW_14.K, SW_32.K, SW_51.K, SW_68.K, SW_69.A, SW_70.A, SW_81.A, SW_83.K, SW_84.K, U2.11
L_CB6: SW_13.K, SW_31.K, SW_50.K, SW_67.K, SW_81.K, U2.12
L_CB7: SW_12.K, SW_30.K, SW_49.K, SW_66.K, SW_83.A, SW_84.A, SW_87.A, SW_88.A, SW_89.A, SW_90.A, SW_91.A, U2.13
L_CB8: SW_11.K, SW_29.K, SW_48.K, SW_65.K, U2.14
L_CB9: SW_10.K, SW_28.K, SW_47.K, SW_64.K, U2.15
MISO: P2.1, U1.13
MOSI: P2.4, U1.12
unnamed: C1.1, U1.24, Y1.1
unnamed: C2.1, U1.23, Y1.2
unnamed: C3.1, U1.7
unnamed: C4.1, U1.62
unnamed: C12.1, U2.16
unnamed: C15.1, U3.16
unnamed: D1.2, SW_1.SW2
unnamed: D2.2, SW_2.SW2
unnamed: D3.2, SW_3.SW2
unnamed: D4.2, SW_4.SW2
unnamed: D5.2, SW_5.SW2
unnamed: D6.2, SW_6.SW2
unnamed: D7.2, SW_7.SW2
unnamed: D8.2, SW_8.SW2
unnamed: D9.2, SW_9.SW2
unnamed: D10.2, SW_10.SW2
unnamed: D11.2, SW_11.SW2
unnamed: D12.2, SW_12.SW2
unnamed: D13.2, SW_13.SW2
unnamed: D14.2, SW_14.SW2
unnamed: D15.2, SW_15.SW2
unnamed: D16.2, SW_16.SW2
unnamed: D17.2, SW_17.SW2
unnamed: D18.2, SW_18.SW2
unnamed: D19.2, SW_19.SW2
unnamed: D20.2, SW_20.SW2
unnamed: D21.2, SW_21.SW2
unnamed: D22.2, SW_22.SW2
unnamed: D23.2, SW_23.SW2
unnamed: D24.2, SW_24.SW2
unnamed: D25.2, SW_25.SW2
unnamed: D26.2, SW_26.SW2
unnamed: D27.2, SW_27.SW2
unnamed: D28.2, SW_28.SW2
unnamed: D29.2, SW_29.SW2
unnamed: D30.2, SW_30.SW2
unnamed: D31.2, SW_31.SW2
unnamed: D32.2, SW_32.SW2
unnamed: D33.2, SW_33.SW2
unnamed: D34.2, SW_34.SW2, SW_35.SW2
unnamed: D36.2, SW_36.SW2
unnamed: D37.2, SW_37.SW2
unnamed: D38.2, SW_38.SW2
unnamed: D39.2, SW_39.SW2
unnamed: D40.2, SW_40.SW2, SW_40_2.SW1
unnamed: D41.2, SW_41.SW2
unnamed: D42.2, SW_42.SW2
unnamed: D43.2, SW_43.SW2
unnamed: D44.2, SW_44.SW2
unnamed: D45.2, SW_45.SW2
unnamed: D46.2, SW_46.SW2
unnamed: D47.2, SW_47.SW2
unnamed: D48.2, SW_48.SW2
unnamed: D49.2, SW_49.SW2
unnamed: D50.2, SW_50.SW2
unnamed: D51.2, SW_51.SW2
unnamed: D53.2, SW_52.SW2, SW_53.SW2
unnamed: D54.2, SW_54.SW2
unnamed: D55.2, SW_55.SW2
unnamed: D57.2, SW_56.SW2, SW_57.SW2
unnamed: D58.2, SW_58.SW2
unnamed: D59.2, SW_59.SW2
unnamed: D60.2, SW_60.SW2
unnamed: D61.2, SW_61.SW2
unnamed: D62.2, SW_62.SW2
unnamed: D63.2, SW_63.SW2
unnamed: D64.2, SW_64.SW2
unnamed: D65.2, SW_65.SW2
unnamed: D66.2, SW_66.SW2
unnamed: D67.2, SW_67.SW2
unnamed: D68.2, SW_68.SW2
unnamed: D69.2, SW_69.SW2
unnamed: D70.2, SW_70.SW2
unnamed: D71.2, SW_71.SW2
unnamed: D72.2, SW_72.SW2
unnamed: D73.2, SW_73.SW2, SW_74.SW2
unnamed: D75.2, SW_75.SW2, SW_76.SW1
unnamed: D77.2, SW_77.SW2, SW_78.SW1
unnamed: D79.2, SW_79.SW2, SW_80.SW2
unnamed: D81.2, SW_81.SW2
unnamed: D82.2, SW_83.SW2, SW_84.SW1
unnamed: D85.2, SW_87.SW1, SW_88.SW1
unnamed: D89.2, SW_89.SW2
unnamed: D90.2, SW_90.SW2
unnamed: D91.2, SW_91.SW2
unnamed: F1.1, P1.1
unnamed: R6.1, RGB33.2
unnamed: R7.1, RGB33.3
unnamed: R8.1, RGB33.4
unnamed: R11.1, U2.3
unnamed: R12.1, U2.6
unnamed: R13.1, U3.3
unnamed: R14.1, U3.6
PWM_BLUE: R8.2, U1.17
PWM_GREEN: R7.2, U1.16
PWM_RED: R6.2, U1.15
R1: D1.1, D2.1, D3.1, D4.1, D5.1, D6.1, D7.1, D8.1, D9.1, D10.1, D11.1, D12.1, D13.1, D14.1, D15.1, D16.1, D17.1, D18.1, U1.27
R2: D19.1, D20.1, D21.1, D22.1, D23.1, D24.1, D25.1, D26.1, D27.1, D28.1, D29.1, D30.1, D31.1, D32.1, D33.1, D34.1, D36.1, D37.1, U1.28
R3: D38.1, D39.1, D40.1, D41.1, D42.1, D43.1, D44.1, D45.1, D46.1, D47.1, D48.1, D49.1, D50.1, D51.1, D53.1, U1.29
R4: D54.1, D55.1, D57.1, D58.1, D59.1, D60.1, D61.1, D62.1, D63.1, D64.1, D65.1, D66.1, D67.1, D68.1, D69.1, D70.1, U1.30
R5: D71.1, D72.1, D73.1, D75.1, D77.1, D79.1, D81.1, D82.1, D85.1, D89.1, D90.1, D91.1, U1.31
RESET: P2.5, P3.6, R1.2, SW1.2, U1.20
R_CA1: RGB1.2, RGB2.2, RGB3.2, RGB4.2, RGB5.2, RGB6.2, RGB7.2, RGB8.2, RGB8_2.2, RGB9.1, U3.21
R_CA2: RGB1.1, RGB2.3, RGB3.3, RGB4.3, RGB5.3, RGB6.3, RGB7.3, RGB8.3, RGB8_2.3, U3.22
R_CA3: RGB1.3, RGB2.1, RGB3.4, RGB4.4, RGB5.4, RGB6.4, RGB7.4, RGB8.4, RGB8_2.4, RGB11.1, U3.23
R_CA4: RGB1.4, RGB2.4, RGB3.1, RGB12.1, U3.24
R_CA5: RGB4.1, RGB13.1, RGB13_2.1, U3.25
R_CA6: RGB5.1, RGB14.1, RGB14_2.1, RGB16.4, U3.26
R_CA7: RGB6.1, RGB9.4, RGB10.4, RGB11.4, RGB12.4, RGB13.4, RGB13_2.4, RGB14.4, RGB14_2.4, RGB16.3, U3.27
R_CA8: RGB7.1, RGB9.3, RGB10.3, RGB11.3, RGB12.3, RGB13.3, RGB13_2.3, RGB14.3, RGB14_2.3, RGB16.1, U3.28
R_CA9: RGB8.1, RGB8_2.1, RGB9.2, RGB10.2, RGB11.2, RGB12.2, RGB13.2, RGB13_2.2, RGB14.2, RGB14_2.2, RGB16.2, U3.1
R_CB1: RGB17.2, RGB18.2, RGB19.2, RGB20.2, RGB21.2, RGB22.2, RGB24.2, RGB25.1, U3.7
R_CB2: RGB17.1, RGB18.3, RGB19.3, RGB20.3, RGB21.3, RGB22.3, RGB24.3, U3.8
R_CB3: RGB17.3, RGB18.1, RGB19.4, RGB20.4, RGB21.4, RGB22.4, RGB24.4, U3.9
R_CB4: RGB17.4, RGB18.4, RGB19.1, RGB28.1, U3.10
R_CB5: RGB20.1, U3.11
R_CB6: RGB21.1, RGB30.1, RGB31.4, RGB32.4, U3.12
R_CB7: RGB22.1, RGB25.4, RGB28.4, RGB30.4, RGB31.1, RGB32.3, U3.13
R_CB8: RGB25.3, RGB28.3, RGB30.3, RGB31.3, RGB32.1, U3.14
R_CB9: RGB24.1, RGB25.2, RGB28.2, RGB30.2, RGB31.2, RGB32.2, U3.15
SCK: P2.3, U1.11
TCK: P3.1, U1.57
TDI: P3.9, U1.54
TDO: P3.3, U1.55
TMS: P3.5, U1.56
USB+: P1.3, R5.2
USB-: P1.2, R4.2
